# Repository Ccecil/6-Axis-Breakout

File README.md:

6 Axis Breakout

This is a breakout board designed to expand the V2 Smoothieboard in order to use up to 6 axis.  It gives the breakouts for step/dir/en along with endstops for the axes and connections which are not on the mainboard.
It uses 4 of the Gadgeteer headers to add these functions:

-Step/Dir/En for all 6 axes (bidirectional level shifted)

-Endstop min/max for ABC axes (buffered and identical to the XYZ Endstops on the mainboard)

-4 small FETs (2n7002) which are connected to HWPWM so they can be used for things like hobby servos, BLtouch, small devices, etc. 

-UART0 breakout (bidirectional level shifted)

-EStop input (bidirectional level shifted)

-Vfet in for supplying a voltage other than 5v to run things like hobby servos.  (Jumper selected and disabled by default. 5v default voltage to header)

-Header to breakout all functions to a daughterboard or large single harness.  (i.e. Parallel port connector board for retrofitting existing machines)

PDF Schematic https://github.com/Ccecil/6-Axis-Breakout/blob/main/6AxisBreakout/6AxisBreakout.pdf

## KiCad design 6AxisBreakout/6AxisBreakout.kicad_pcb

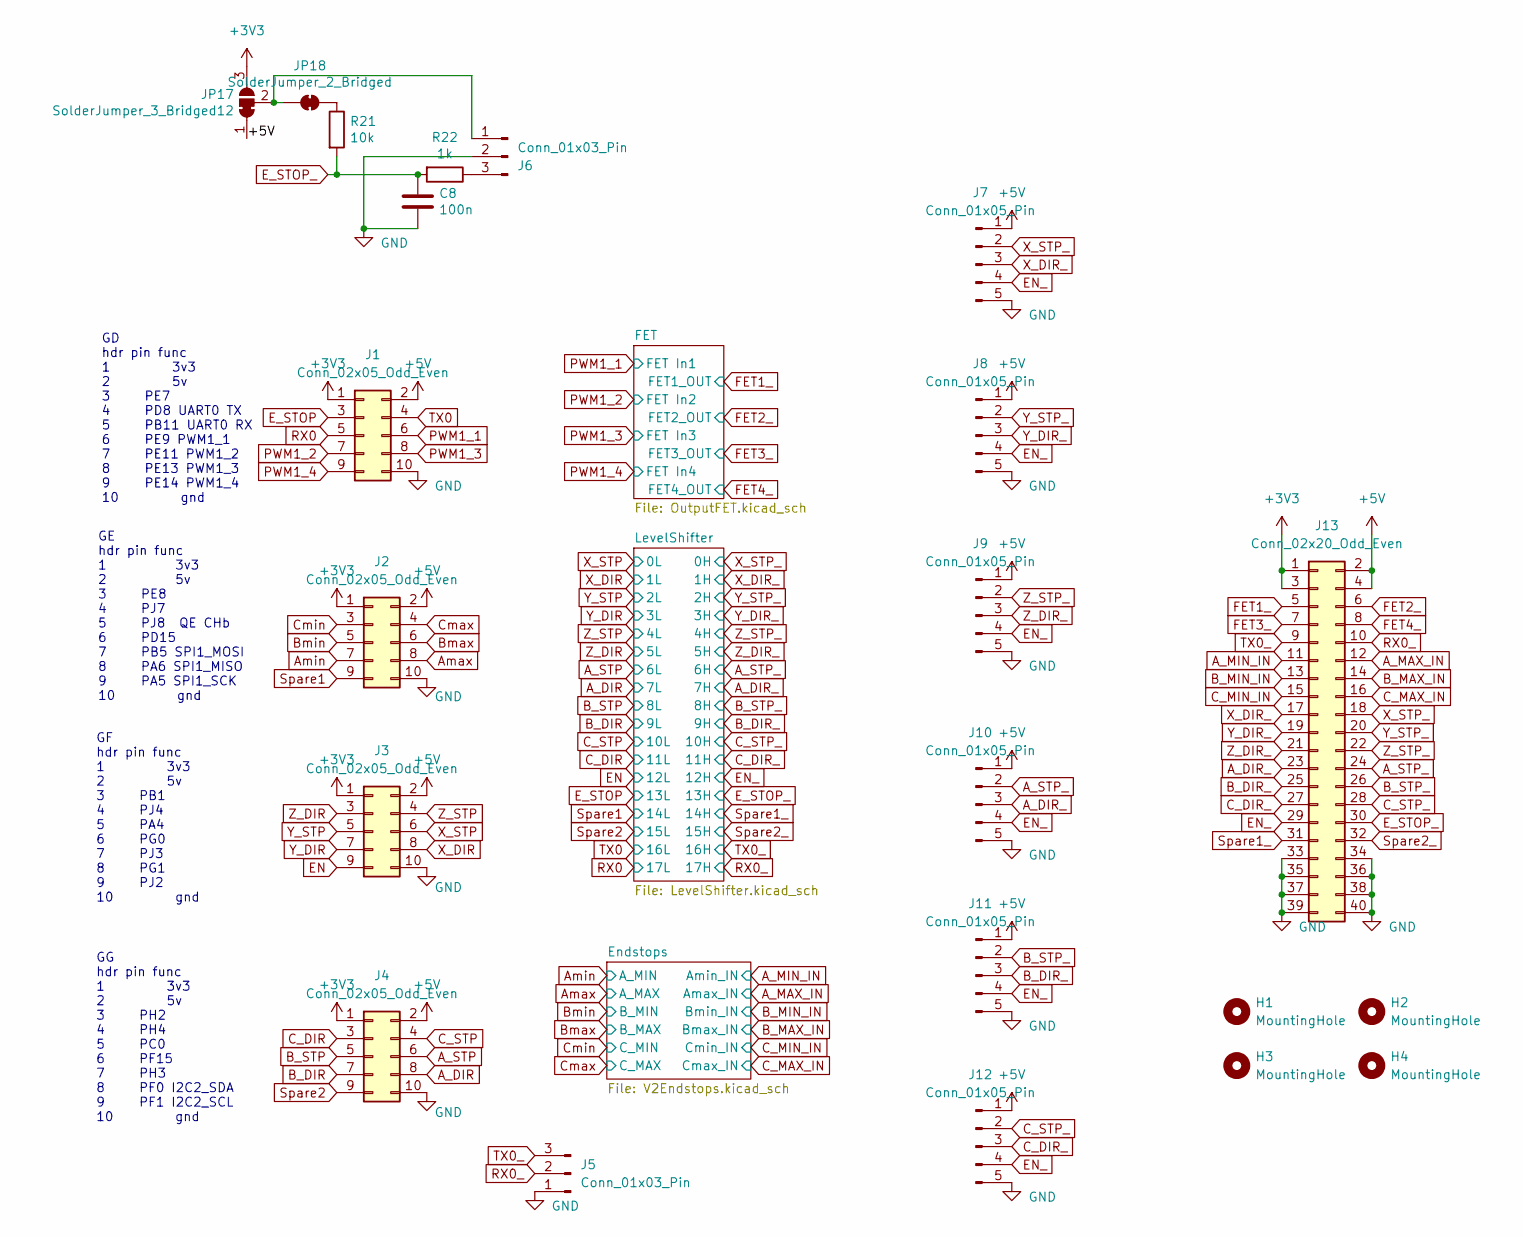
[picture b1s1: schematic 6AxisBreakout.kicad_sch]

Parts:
C8: 100n; C_0402_1005Metric
H1, H2, H3, H4: MountingHole; MountingHole_3.2mm_M3
J1, J2, J3, J4: Conn_02x05_Odd_Even; PinHeader_2x05_P1.27mm_Vertical_SMD
J5, J6: Conn_01x03_Pin; Molex_KK-254_AE-6410-03A_1x03_P2.54mm_Vertical
J7, J8, J9, J10, J11, J12: Conn_01x05_Pin; Molex_KK-254_AE-6410-05A_1x05_P2.54mm_Vertical
J13: Conn_02x20_Odd_Even; PinHeader_2x20_P2.54mm_Vertical
JP17: SolderJumper_3_Bridged12; SolderJumper-3_P1.3mm_Bridged12_RoundedPad1.0x1.5mm
JP18: SolderJumper_2_Bridged; SolderJumper-2_P1.3mm_Bridged2Bar_RoundedPad1.0x1.5mm
R21: 10k; R_0402_1005Metric
R22: 1k; R_0402_1005Metric

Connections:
+3V3: J1.1, J2.1, J3.1, J4.1, J13.1, J13.3, JP17.3 (B); also elsewhere on the board
+5V: J1.2, J2.2, J3.2, J4.2, J7.1, J8.1, J9.1, J10.1, J11.1, J12.1, J13.2, J13.4, JP17.1 (A); also elsewhere on the board
A_DIR: J4.8; also elsewhere on the board
A_DIR_: J10.3, J13.23; also elsewhere on the board
A_MAX_IN: J13.12; also elsewhere on the board
A_MIN_IN: J13.11; also elsewhere on the board
A_STP: J4.6; also elsewhere on the board
A_STP_: J10.2, J13.24; also elsewhere on the board
Amax: J2.8; also elsewhere on the board
Amin: J2.7; also elsewhere on the board
B_DIR: J4.7; also elsewhere on the board
B_DIR_: J11.3, J13.25; also elsewhere on the board
B_MAX_IN: J13.14; also elsewhere on the board
B_MIN_IN: J13.13; also elsewhere on the board
B_STP: J4.5; also elsewhere on the board
B_STP_: J11.2, J13.26; also elsewhere on the board
Bmax: J2.6; also elsewhere on the board
Bmin: J2.5; also elsewhere on the board
C_DIR: J4.3; also elsewhere on the board
C_DIR_: J12.3, J13.27; also elsewhere on the board
C_MAX_IN: J13.16; also elsewhere on the board
C_MIN_IN: J13.15; also elsewhere on the board
C_STP: J4.4; also elsewhere on the board
C_STP_: J12.2, J13.28; also elsewhere on the board
Cmax: J2.4; also elsewhere on the board
Cmin: J2.3; also elsewhere on the board
EN: J3.9; also elsewhere on the board
EN_: J7.4, J8.4, J9.4, J10.4, J11.4, J12.4, J13.29; also elsewhere on the board
E_STOP: J1.3; also elsewhere on the board
E_STOP_: C8.1, J13.30, R21.2, R22.2; also elsewhere on the board
FET1_: J13.5; also elsewhere on the board
FET2_: J13.6; also elsewhere on the board
FET3_: J13.7; also elsewhere on the board
FET4_: J13.8; also elsewhere on the board
GND: C8.2, J1.10, J2.10, J3.10, J4.10, J5.1, J6.2, J7.5, J8.5, J9.5, J10.5, J11.5, J12.5, J13.33, J13.34, J13.35, J13.36, J13.37, J13.38, J13.39, J13.40; also elsewhere on the board
unnamed: J6.1, JP17.2 (C), JP18.1 (A)
unnamed: J6.3, R22.1
unnamed: JP18.2 (B), R21.1
PWM1_1: J1.6; also elsewhere on the board
PWM1_2: J1.7; also elsewhere on the board
PWM1_3: J1.8; also elsewhere on the board
PWM1_4: J1.9; also elsewhere on the board
RX0: J1.5; also elsewhere on the board
RX0_: J5.2, J13.10; also elsewhere on the board
Spare1: J2.9; also elsewhere on the board
Spare1_: J13.31; also elsewhere on the board
Spare2: J4.9; also elsewhere on the board
Spare2_: J13.32; also elsewhere on the board
TX0: J1.4; also elsewhere on the board
TX0_: J5.3, J13.9; also elsewhere on the board
X_DIR: J3.8; also elsewhere on the board
X_DIR_: J7.3, J13.17; also elsewhere on the board
X_STP: J3.6; also elsewhere on the board
X_STP_: J7.2, J13.18; also elsewhere on the board
Y_DIR: J3.7; also elsewhere on the board
Y_DIR_: J8.3, J13.19; also elsewhere on the board
Y_STP: J3.5; also elsewhere on the board
Y_STP_: J8.2, J13.20; also elsewhere on the board
Z_DIR: J3.3; also elsewhere on the board
Z_DIR_: J9.3, J13.21; also elsewhere on the board
Z_STP: J3.4; also elsewhere on the board
Z_STP_: J9.2, J13.22; also elsewhere on the board

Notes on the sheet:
GD hdr pin func 1 3v3 2 5v 3 PE7 4 PD8 UART0 TX 5 PB11 UART0 RX 6 PE9 PWM1_1 7 PE11 PWM1_2 8 PE13 PWM1_3 9 PE14 PWM1_4 10 gnd
GF hdr pin func 1 3v3 2 5v 3 PB1 4 PJ4 5 PA4 6 PG0 7 PJ3 8 PG1 9 PJ2 10 gnd
GE hdr pin func 1 3v3 2 5v 3 PE8 4 PJ7 5 PJ8 QE CHb 6 PD15 7 PB5 SPI1_MOSI 8 PA6 SPI1_MISO 9 PA5 SPI1_SCK 10 gnd
GG hdr pin func 1 3v3 2 5v 3 PH2 4 PH4 5 PC0 6 PF15 7 PH3 8 PF0 I2C2_SDA 9 PF1 I2C2_SCL 10 gnd

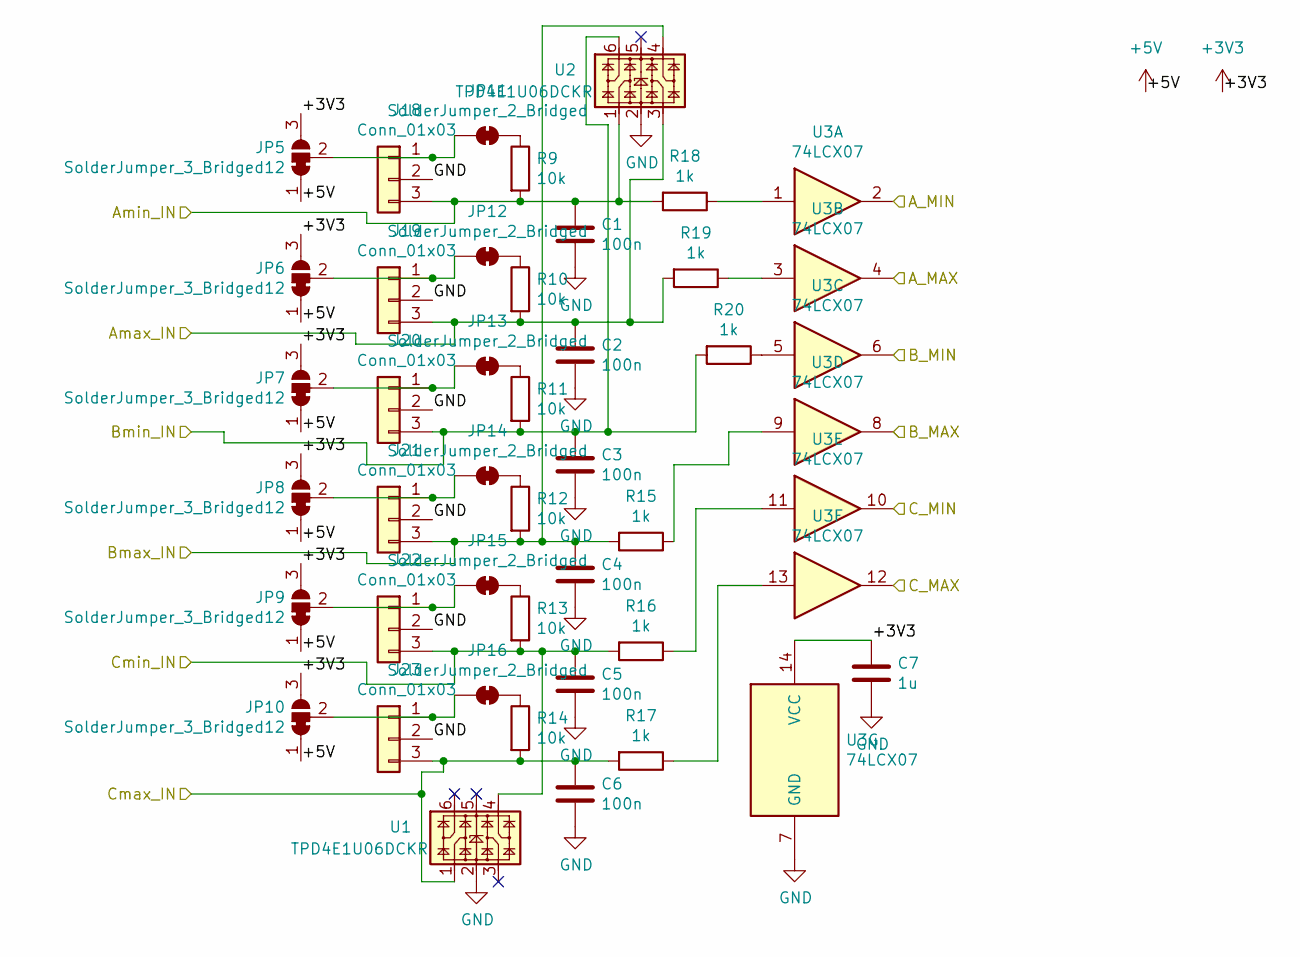
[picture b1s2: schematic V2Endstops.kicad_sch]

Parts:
C1, C2, C3, C4, C5, C6: 100n; C_0402_1005Metric
C7: 1u; C_0402_1005Metric
J18, J19, J20, J21, J22, J23: Conn_01x03; Molex_KK-254_AE-6410-03A_1x03_P2.54mm_Vertical
JP5, JP6, JP7, JP8, JP9, JP10: SolderJumper_3_Bridged12; SolderJumper-3_P1.3mm_Bridged12_RoundedPad1.0x1.5mm
JP11, JP12, JP13, JP14, JP15, JP16: SolderJumper_2_Bridged; SolderJumper-2_P1.3mm_Bridged2Bar_RoundedPad1.0x1.5mm
R9, R10, R11, R12, R13, R14: 10k; R_0402_1005Metric
R15, R16, R17, R18, R19, R20: 1k; R_0402_1005Metric
U1, U2: TPD4E1U06DCKR; SOT-363_SC-70-6
U3: 74LCX07; TSSOP-14_4.4x5mm_P0.65mm

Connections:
+3V3: C7.1, JP5.3 (B), JP6.3 (B), JP7.3 (B), JP8.3 (B), JP9.3 (B), JP10.3 (B), U3.14 (VCC); also elsewhere on the board
+5V: JP5.1 (A), JP6.1 (A), JP7.1 (A), JP8.1 (A), JP9.1 (A), JP10.1 (A); also elsewhere on the board
A_MAX_IN: C2.1, J19.3, R10.2, R19.2, U2.3; also elsewhere on the board
A_MIN_IN: C1.1, J18.3, R9.2, R18.2, U2.1; also elsewhere on the board
Amax: U3.4; also elsewhere on the board
Amin: U3.2; also elsewhere on the board
B_MAX_IN: C4.1, J21.3, R12.2, R15.2, U2.4; also elsewhere on the board
B_MIN_IN: C3.1, J20.3, R11.2, R20.2, U2.6; also elsewhere on the board
Bmax: U3.8; also elsewhere on the board
Bmin: U3.6; also elsewhere on the board
C_MAX_IN: C6.1, J23.3, R14.2, R17.2, U1.1; also elsewhere on the board
C_MIN_IN: C5.1, J22.3, R13.2, R16.2, U1.4; also elsewhere on the board
Cmax: U3.12; also elsewhere on the board
Cmin: U3.10; also elsewhere on the board
GND: C1.2, C2.2, C3.2, C4.2, C5.2, C6.2, C7.2, J18.2, J19.2, J20.2, J21.2, J22.2, J23.2, U1.2, U2.2, U3.7 (GND); also elsewhere on the board
unnamed: J18.1, JP5.2 (C), JP11.1 (A)
unnamed: J19.1, JP6.2 (C), JP12.1 (A)
unnamed: J20.1, JP7.2 (C), JP13.1 (A)
unnamed: J21.1, JP8.2 (C), JP14.1 (A)
unnamed: J22.1, JP9.2 (C), JP15.1 (A)
unnamed: J23.1, JP10.2 (C), JP16.1 (A)
unnamed: JP11.2 (B), R9.1
unnamed: JP12.2 (B), R10.1
unnamed: JP13.2 (B), R11.1
unnamed: JP14.2 (B), R12.1
unnamed: JP15.2 (B), R13.1
unnamed: JP16.2 (B), R14.1
unnamed: R15.1, U3.9
unnamed: R16.1, U3.11
unnamed: R17.1, U3.13
unnamed: R18.1, U3.1
unnamed: R19.1, U3.3
unnamed: R20.1, U3.5

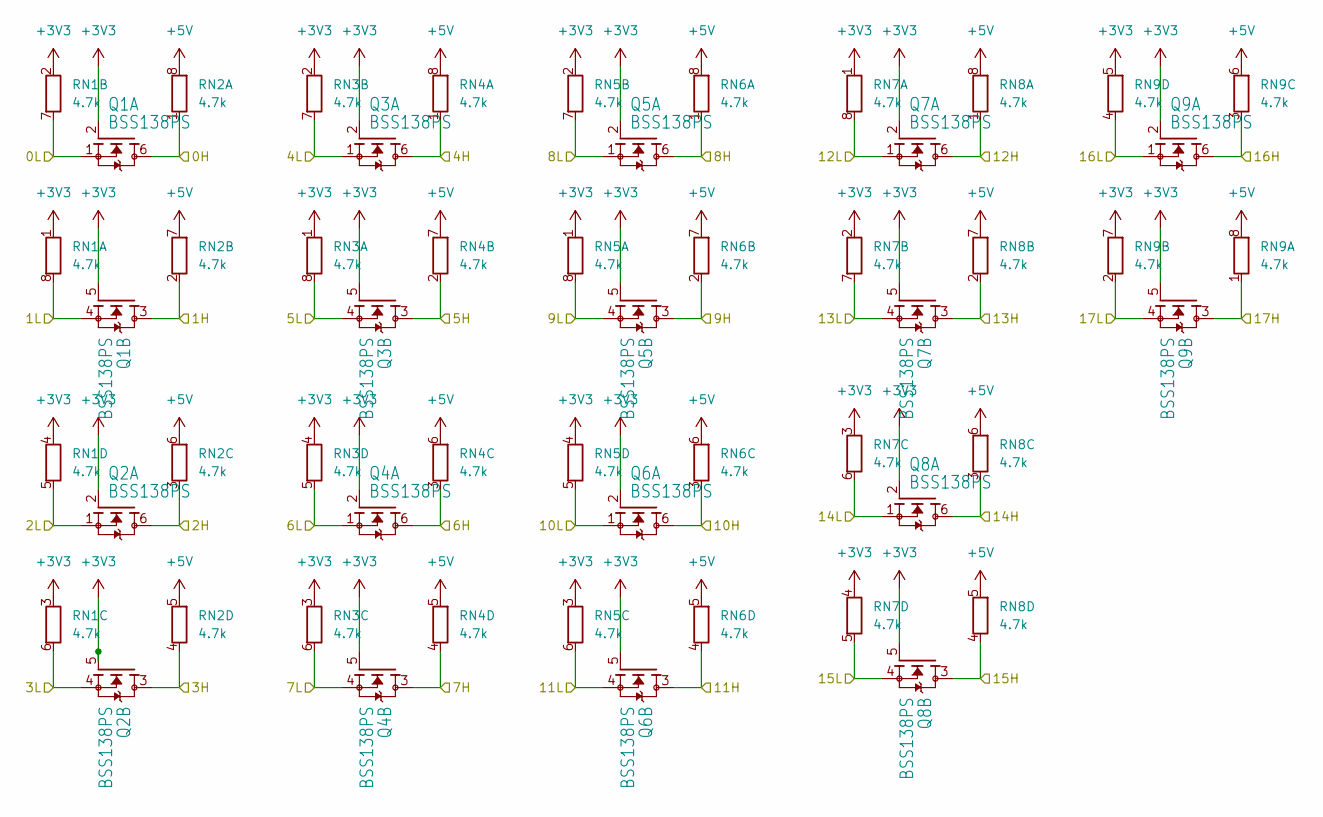
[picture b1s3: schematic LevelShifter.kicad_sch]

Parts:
Q1, Q2, Q3, Q4, Q5, Q6, Q7, Q8, Q9: BSS138PS; SOT-363_SC-70-6
RN1, RN2, RN3, RN4, RN5, RN6, RN7, RN8, RN9: 4.7k; R_Array_Concave_4x0603

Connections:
+3V3: Q1.2 (G), Q1.5 (G), Q2.2 (G), Q2.5 (G), Q3.2 (G), Q3.5 (G), Q4.2 (G), Q4.5 (G), Q5.2 (G), Q5.5 (G), Q6.2 (G), Q6.5 (G), Q7.2 (G), Q7.5 (G), Q8.2 (G), Q8.5 (G), Q9.2 (G), Q9.5 (G), RN1.1 (R1.1), RN1.2 (R2.1), RN1.3 (R3.1), RN1.4 (R4.1), RN3.1 (R1.1), RN3.2 (R2.1), RN3.3 (R3.1), RN3.4 (R4.1), RN5.1 (R1.1), RN5.2 (R2.1), RN5.3 (R3.1), RN5.4 (R4.1), RN7.1 (R1.1), RN7.2 (R2.1), RN7.3 (R3.1), RN7.4 (R4.1), RN9.5 (R4.2), RN9.7 (R2.2); also elsewhere on the board
+5V: RN2.5 (R4.2), RN2.6 (R3.2), RN2.7 (R2.2), RN2.8 (R1.2), RN4.5 (R4.2), RN4.6 (R3.2), RN4.7 (R2.2), RN4.8 (R1.2), RN6.5 (R4.2), RN6.6 (R3.2), RN6.7 (R2.2), RN6.8 (R1.2), RN8.5 (R4.2), RN8.6 (R3.2), RN8.7 (R2.2), RN8.8 (R1.2), RN9.6 (R3.2), RN9.8 (R1.2); also elsewhere on the board
A_DIR: Q4.4 (S), RN3.6 (R3.2); also elsewhere on the board
A_DIR_: Q4.3 (D), RN4.4 (R4.1); also elsewhere on the board
A_STP: Q4.1 (S), RN3.5 (R4.2); also elsewhere on the board
A_STP_: Q4.6 (D), RN4.3 (R3.1); also elsewhere on the board
B_DIR: Q5.4 (S), RN5.8 (R1.2); also elsewhere on the board
B_DIR_: Q5.3 (D), RN6.2 (R2.1); also elsewhere on the board
B_STP: Q5.1 (S), RN5.7 (R2.2); also elsewhere on the board
B_STP_: Q5.6 (D), RN6.1 (R1.1); also elsewhere on the board
C_DIR: Q6.4 (S), RN5.6 (R3.2); also elsewhere on the board
C_DIR_: Q6.3 (D), RN6.4 (R4.1); also elsewhere on the board
C_STP: Q6.1 (S), RN5.5 (R4.2); also elsewhere on the board
C_STP_: Q6.6 (D), RN6.3 (R3.1); also elsewhere on the board
EN: Q7.1 (S), RN7.8 (R1.2); also elsewhere on the board
EN_: Q7.6 (D), RN8.1 (R1.1); also elsewhere on the board
E_STOP: Q7.4 (S), RN7.7 (R2.2); also elsewhere on the board
E_STOP_: Q7.3 (D), RN8.2 (R2.1); also elsewhere on the board
RX0: Q9.4 (S), RN9.2 (R2.1); also elsewhere on the board
RX0_: Q9.3 (D), RN9.1 (R1.1); also elsewhere on the board
Spare1: Q8.1 (S), RN7.6 (R3.2); also elsewhere on the board
Spare1_: Q8.6 (D), RN8.3 (R3.1); also elsewhere on the board
Spare2: Q8.4 (S), RN7.5 (R4.2); also elsewhere on the board
Spare2_: Q8.3 (D), RN8.4 (R4.1); also elsewhere on the board
TX0: Q9.1 (S), RN9.4 (R4.1); also elsewhere on the board
TX0_: Q9.6 (D), RN9.3 (R3.1); also elsewhere on the board
X_DIR: Q1.4 (S), RN1.8 (R1.2); also elsewhere on the board
X_DIR_: Q1.3 (D), RN2.2 (R2.1); also elsewhere on the board
X_STP: Q1.1 (S), RN1.7 (R2.2); also elsewhere on the board
X_STP_: Q1.6 (D), RN2.1 (R1.1); also elsewhere on the board
Y_DIR: Q2.4 (S), RN1.6 (R3.2); also elsewhere on the board
Y_DIR_: Q2.3 (D), RN2.4 (R4.1); also elsewhere on the board
Y_STP: Q2.1 (S), RN1.5 (R4.2); also elsewhere on the board
Y_STP_: Q2.6 (D), RN2.3 (R3.1); also elsewhere on the board
Z_DIR: Q3.4 (S), RN3.8 (R1.2); also elsewhere on the board
Z_DIR_: Q3.3 (D), RN4.2 (R2.1); also elsewhere on the board
Z_STP: Q3.1 (S), RN3.7 (R2.2); also elsewhere on the board
Z_STP_: Q3.6 (D), RN4.1 (R1.1); also elsewhere on the board

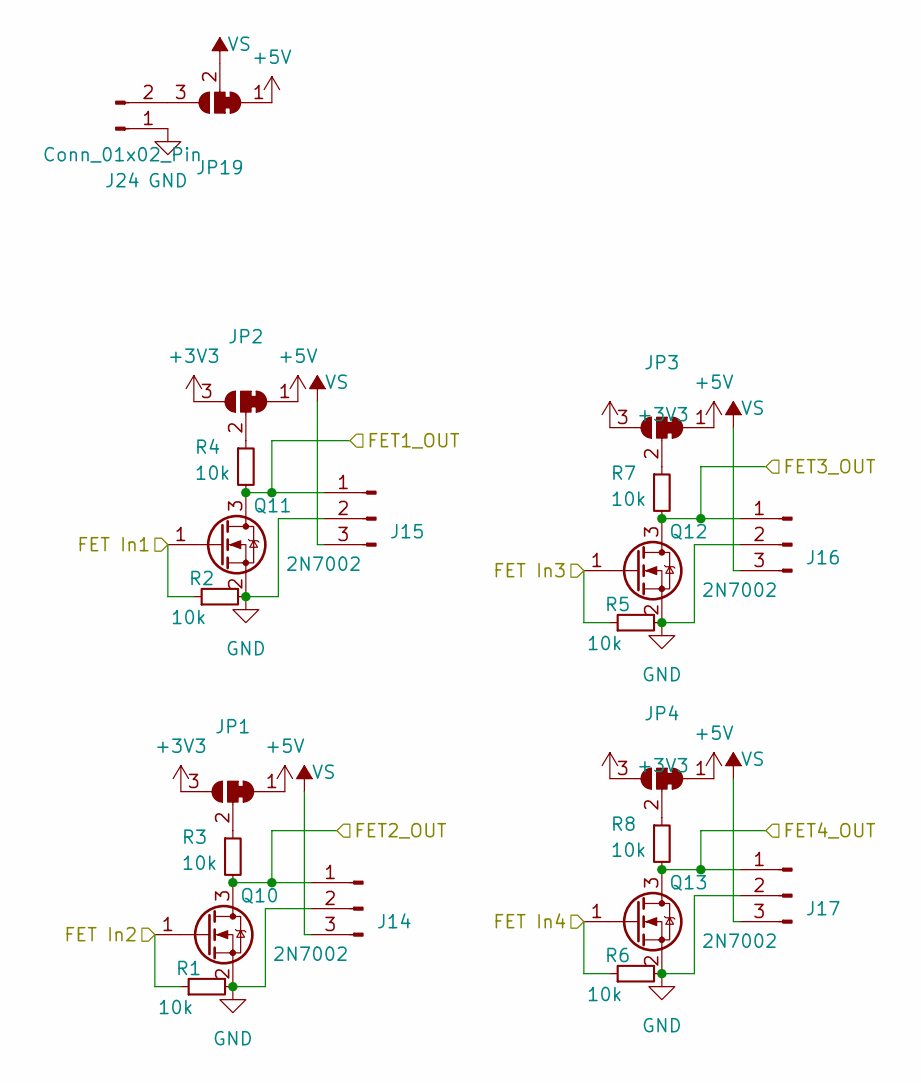
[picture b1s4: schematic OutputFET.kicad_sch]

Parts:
J14, J15, J16, J17: Conn_01x03_Pin; Molex_KK-254_AE-6410-03A_1x03_P2.54mm_Vertical
J24: Conn_01x02_Pin; Molex_KK-254_AE-6410-02A_1x02_P2.54mm_Vertical
JP1, JP2, JP3, JP4, JP19: SolderJumper_3_Bridged12; SolderJumper-3_P1.3mm_Bridged12_RoundedPad1.0x1.5mm
Q10, Q11, Q12, Q13: 2N7002; SOT-23
R1, R2, R3, R4, R5, R6, R7, R8: 10k; R_0402_1005Metric

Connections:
+3V3: JP1.3 (B), JP2.3 (B), JP3.3 (B), JP4.3 (B); also elsewhere on the board
+5V: JP1.1 (A), JP2.1 (A), JP3.1 (A), JP4.1 (A), JP19.1 (A); also elsewhere on the board
FET1_: J15.1, Q11.3 (D), R4.2; also elsewhere on the board
FET2_: J14.1, Q10.3 (D), R3.2; also elsewhere on the board
FET3_: J16.1, Q12.3 (D), R7.2; also elsewhere on the board
FET4_: J17.1, Q13.3 (D), R8.2; also elsewhere on the board
GND: J14.2, J15.2, J16.2, J17.2, J24.1, Q10.2 (S), Q11.2 (S), Q12.2 (S), Q13.2 (S), R1.2, R2.2, R5.2, R6.2; also elsewhere on the board
unnamed: J24.2, JP19.3 (B)
unnamed: JP1.2 (C), R3.1
unnamed: JP2.2 (C), R4.1
unnamed: JP3.2 (C), R7.1
unnamed: JP4.2 (C), R8.1
PWM1_1: Q11.1 (G), R2.1; also elsewhere on the board
PWM1_2: Q10.1 (G), R1.1; also elsewhere on the board
PWM1_3: Q12.1 (G), R5.1; also elsewhere on the board
PWM1_4: Q13.1 (G), R6.1; also elsewhere on the board
VS: J14.3, J15.3, J16.3, J17.3, JP19.2 (C)

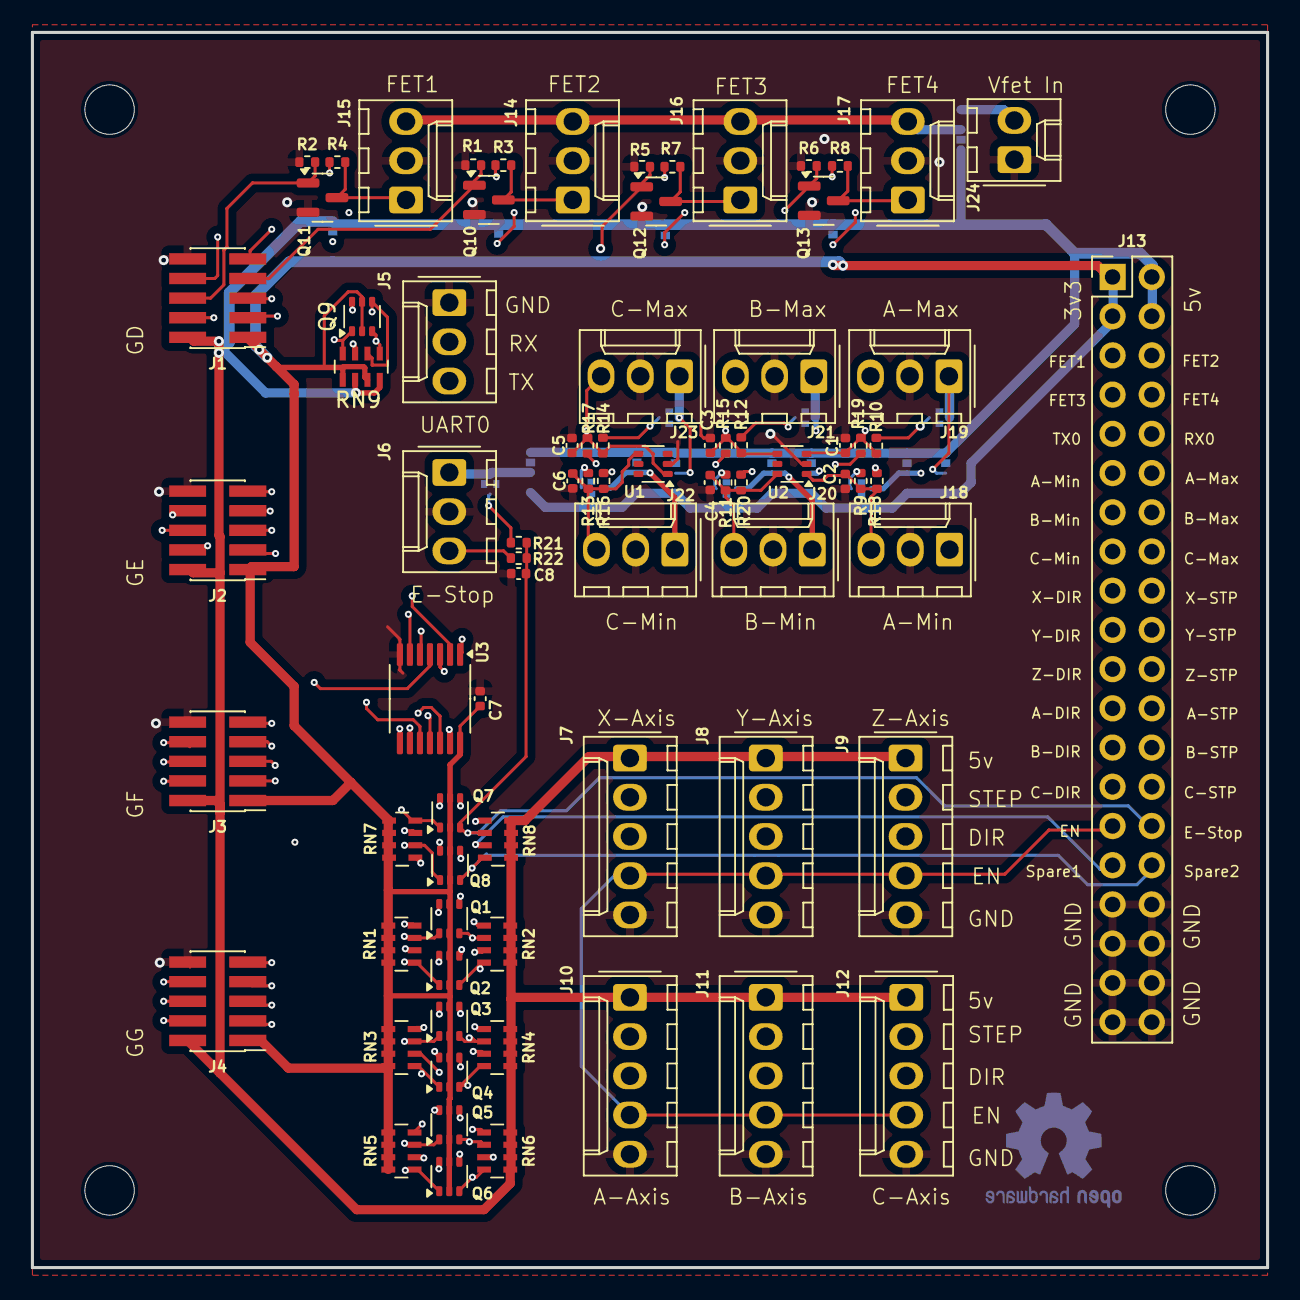
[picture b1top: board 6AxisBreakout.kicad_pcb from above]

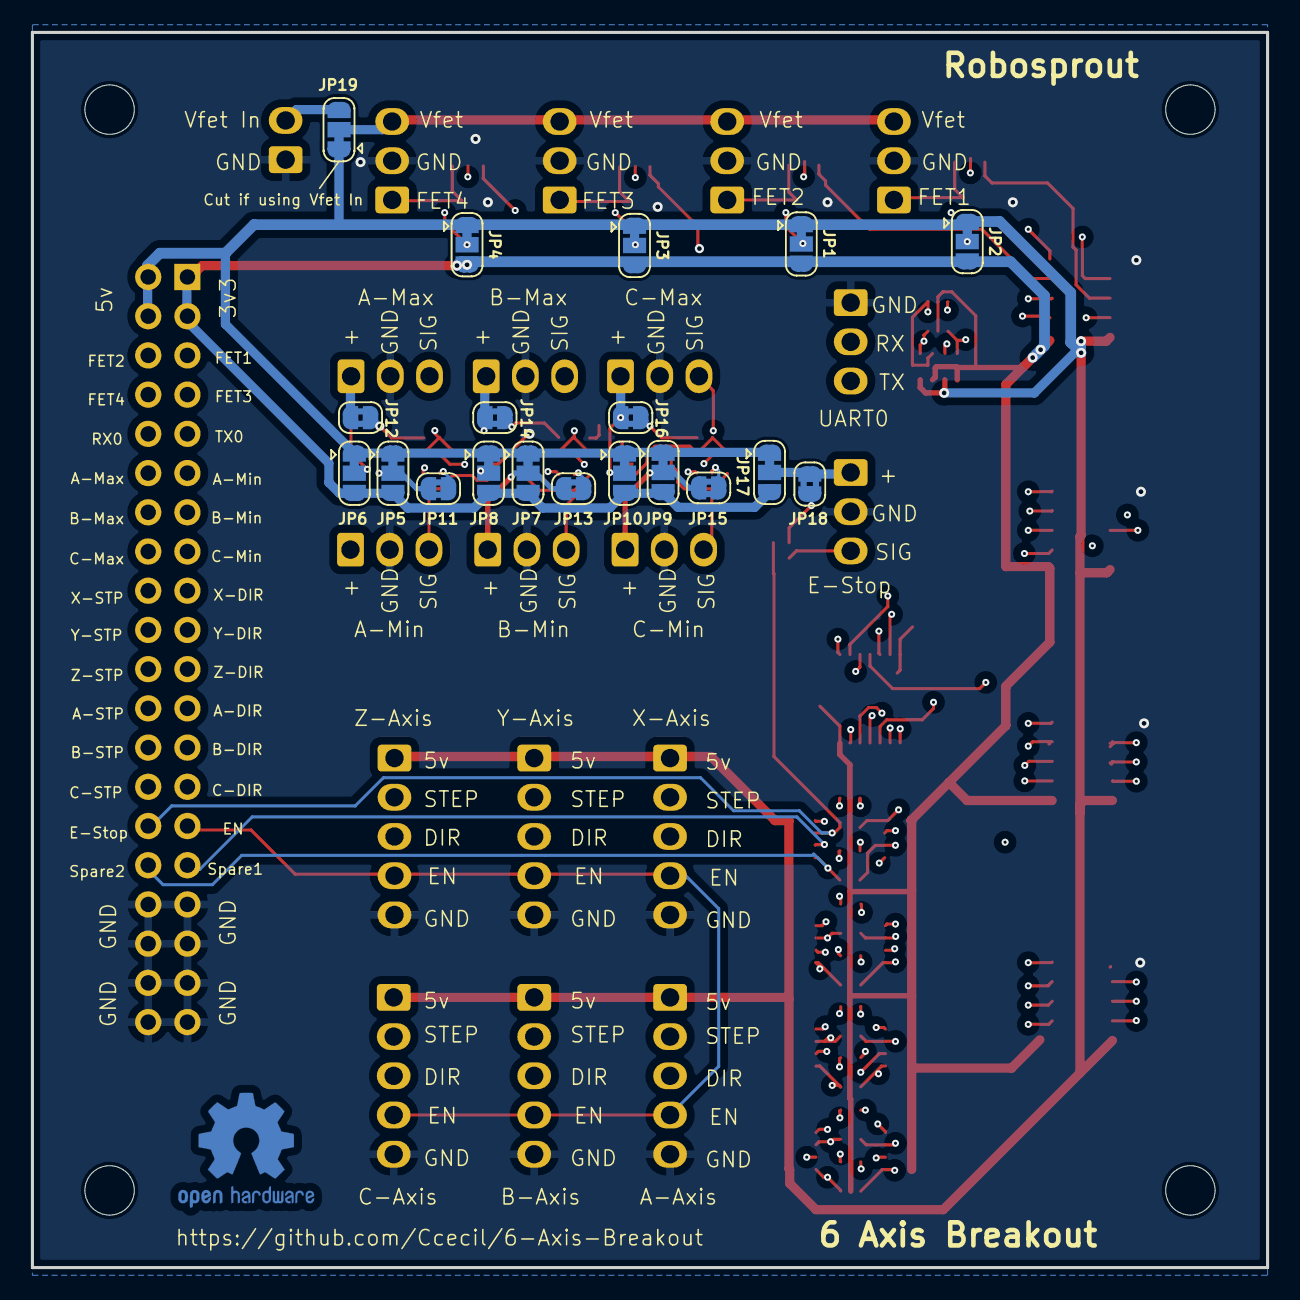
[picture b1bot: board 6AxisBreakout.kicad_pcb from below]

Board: 4 copper layers, 80.0 x 80.0 mm, 102 parts (19 on the bottom side), 86 nets.

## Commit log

2025-12-03 Initial Upload
2025-12-04 Update README.md
    Added PDF schematic link
2026-03-17 add bom
